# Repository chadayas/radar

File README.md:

# In Progress
repo will stay little messy till hardware design is finished.

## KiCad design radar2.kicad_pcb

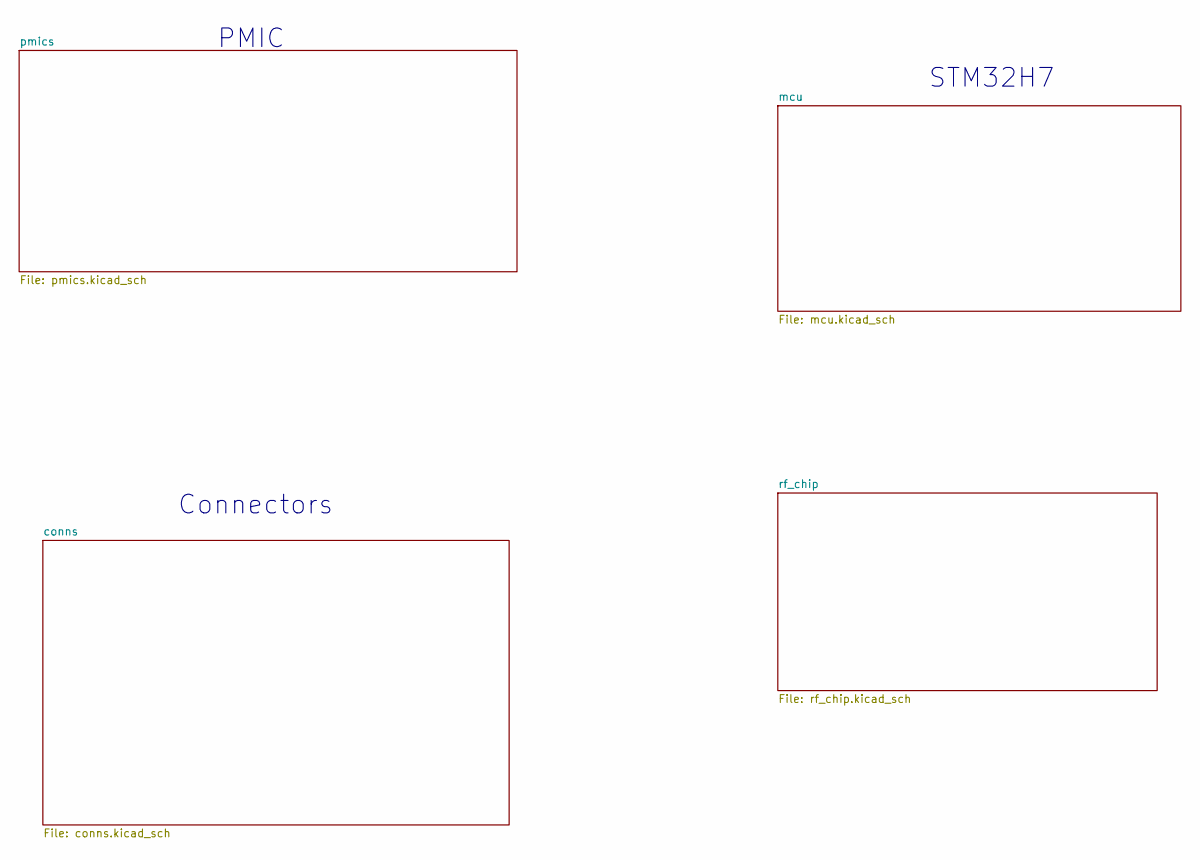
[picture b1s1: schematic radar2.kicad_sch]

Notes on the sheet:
PMIC
Connectors
STM32H7

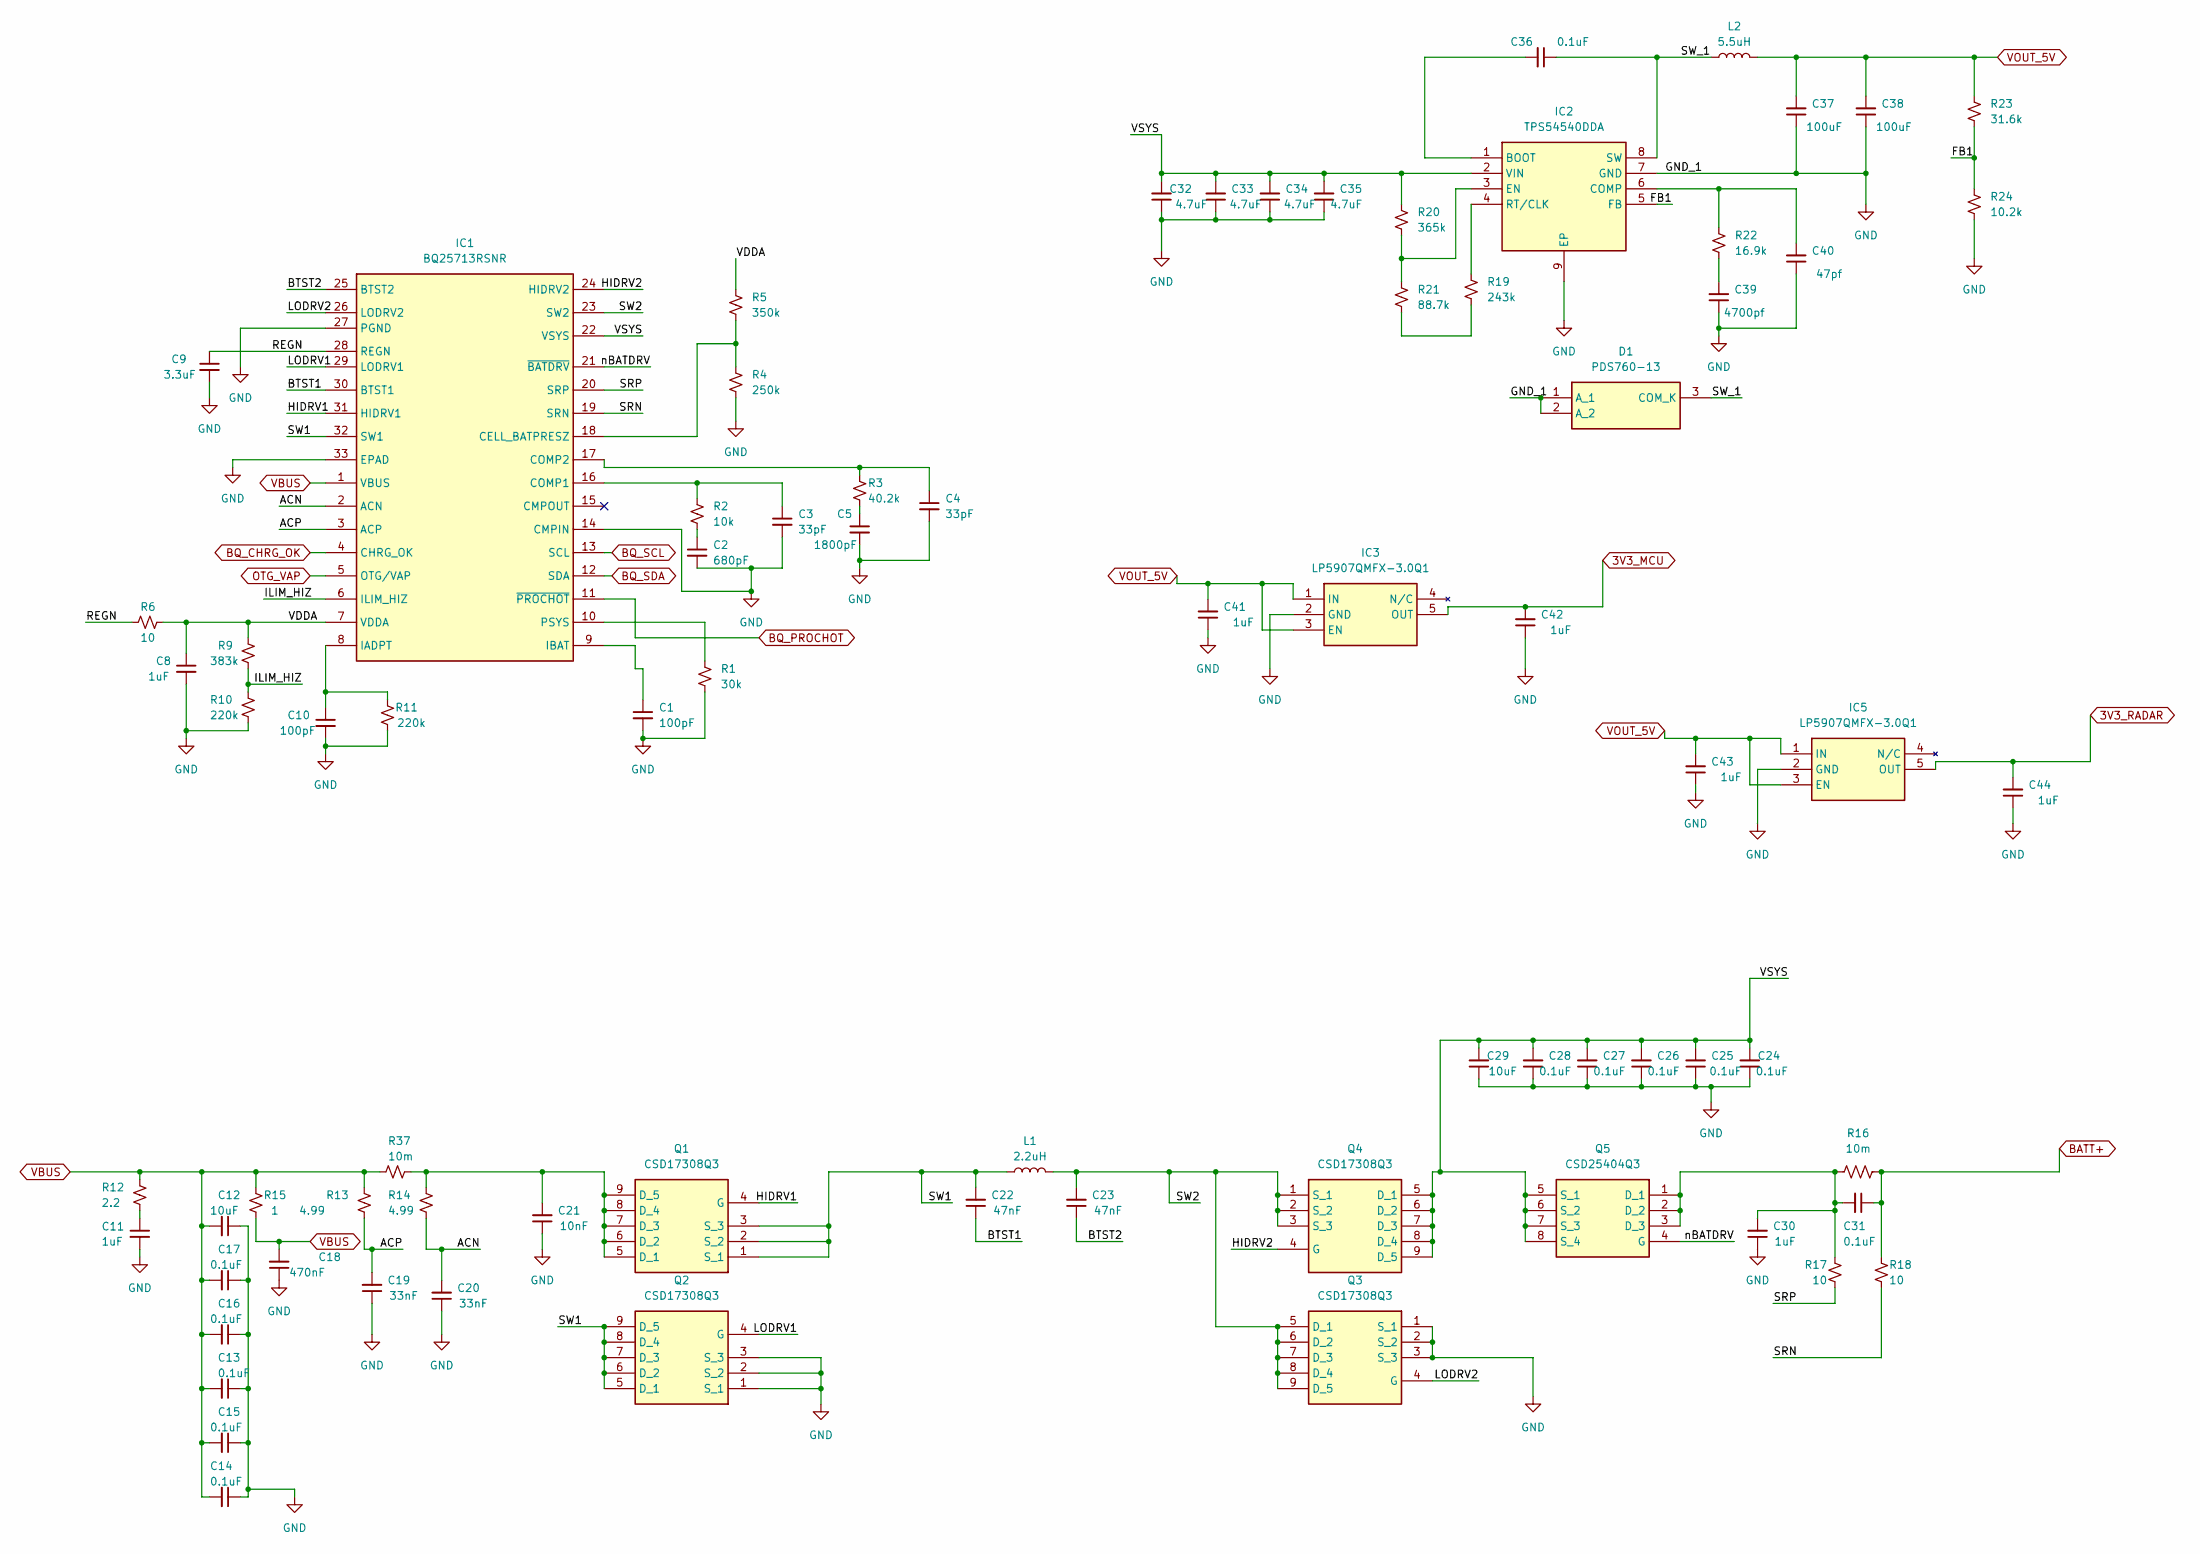
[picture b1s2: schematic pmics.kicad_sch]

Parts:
C1, C10: 100pF; C_0402_1005Metric
C2: 680pF; C_0402_1005Metric
C3, C4: 33pF; C_0402_1005Metric
C5: 1800pF; C_0402_1005Metric
C8, C30: 1uF; C_0402_1005Metric
C9: 3.3uF; C_0402_1005Metric
C11, C41, C42, C43, C44: 1uF; C_0603_1608Metric
C12: 10uF; C_0402_1005Metric
C13, C14, C15, C16, C17, C24, C25, C26, C27, C28, C31: 0.1uF; C_0402_1005Metric
C18: 470nF; C_0402_1005Metric
C19, C20: 33nF; C_0603_1608Metric
C21: 10nF; C_0603_1608Metric
C22, C23: 47nF; C_0402_1005Metric
C29: 10uF; C_0603_1608Metric
C32, C33, C34, C35: 4.7uF; C_0603_1608Metric
C36: 0.1uF; C_0603_1608Metric
C37, C38: 100uF; C_0603_1608Metric
C39: 4700pf; C_0603_1608Metric
C40: 47pf; C_0603_1608Metric
D1: PDS760-13; POWERDI5; Mouser Part Number 621-PDS760-F
IC1: BQ25713RSNR; QFN40P400X400X80-33N-D; Mouser Part Number 595-BQ25713RSNR
IC2: TPS54540DDA; SOIC127P600X170-9N; Mouser Part Number 595-TPS54540DDA
IC3, IC5: LP5907QMFX-3.0Q1; SOT95P280X145-5N; Mouser Part Number 595-LP5907QMFX-3.0Q1
L1: 2.2uH; INDPM9785X300N
L2: 5.5uH; L_0603_1608Metric
Q1, Q2, Q3, Q4: CSD17308Q3; Mouser Part Number 595-CSD17308Q3
Q5: CSD25404Q3; DQG_VSON-CLIP; Mouser Part Number 595-CSD25404Q3
R1: 30k; R_0402_1005Metric
R2: 10k; R_0402_1005Metric
R3: 40.2k; R_0402_1005Metric
R4: 250k; R_0402_1005Metric
R5: 350k; R_0402_1005Metric
R6, R17, R18: 10; R_0402_1005Metric
R9: 383k; R_0402_1005Metric
R10, R11: 220k; R_0402_1005Metric
R12: 2.2; R_0603_1608Metric
R13, R14: 4.99; R_0603_1608Metric
R15: 1; R_0603_1608Metric
R16: 10m; R_0402_1005Metric
R19: 243k; R_0603_1608Metric
R20: 365k; R_0603_1608Metric
R21: 88.7k; R_0603_1608Metric
R22: 16.9k; R_0603_1608Metric
R23: 31.6k; R_0603_1608Metric
R24: 10.2k; R_0603_1608Metric
R37: 10m; R_0603_1608Metric

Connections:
3V3_MCU: C42.2, IC3.5 (OUT); also elsewhere on the board
/pmics/ACN: C20.2, IC1.2 (ACN), R14.1
/pmics/ACP: C19.2, IC1.3 (ACP), R13.1
/pmics/BTST1: C22.1, IC1.30 (BTST1)
/pmics/BTST2: C23.1, IC1.25 (BTST2)
/pmics/FB1: IC2.5 (FB), R23.2, R24.1
/pmics/HIDRV1: IC1.31 (HIDRV1), Q1.4 (G)
/pmics/HIDRV2: IC1.24 (HIDRV2), Q4.4 (G)
/pmics/ILIM_HIZ: IC1.6 (ILIM_HIZ), R9.2, R10.2
/pmics/LODRV1: IC1.29 (LODRV1), Q2.4 (G)
/pmics/LODRV2: IC1.26 (LODRV2), Q3.4 (G)
/pmics/REGN: C9.1, IC1.28 (REGN), R6.2
/pmics/SRN: IC1.19 (SRN), R18.2
/pmics/SRP: IC1.20 (SRP), R17.1
/pmics/SW1: C22.2, IC1.32 (SW1), L1.1, Q1.1 (S_1), Q1.2 (S_2), Q1.3 (S_3), Q2.5 (D_1), Q2.6 (D_2), Q2.7 (D_3), Q2.8 (D_4), Q2.9 (D_5)
/pmics/SW2: C23.2, IC1.23 (SW2), L1.2, Q3.5 (D_1), Q3.6 (D_2), Q3.7 (D_3), Q3.8 (D_4), Q3.9 (D_5), Q4.1 (S_1), Q4.2 (S_2), Q4.3 (S_3)
/pmics/SW_1: C36.1, D1.3 (COM_K), IC2.8 (SW), L2.1
/pmics/VDDA: C8.1, IC1.7 (VDDA), R5.2, R6.1, R9.1
/pmics/VSYS: C24.2, C25.2, C26.2, C27.2, C28.2, C29.2, C32.2, C33.2, C34.2, C35.2, IC1.22 (VSYS), IC2.2 (VIN), Q4.5 (D_1), Q4.6 (D_2), Q4.7 (D_3), Q4.8 (D_4), Q4.9 (D_5), Q5.5 (S_1), Q5.6 (S_2), Q5.7 (S_3), Q5.8 (S_4), Q5.9, R20.1
/pmics/nBATDRV: IC1.21 (~BATDRV), Q5.4 (G)
BATT+: C31.1, R16.2, R18.1; also elsewhere on the board
BQ_CHRG_OK: IC1.4 (CHRG_OK); also elsewhere on the board
BQ_PROCHOT: IC1.11 (~PROCHOT); also elsewhere on the board
BQ_SCL: IC1.13 (SCL); also elsewhere on the board
BQ_SDA: IC1.12 (SDA); also elsewhere on the board
unnamed: C2.1, R2.2
unnamed: C5.1, R3.1
unnamed: C11.1, R12.1
unnamed: C39.2, R22.2
unnamed: IC1.18 (CELL_BATPRESZ), R4.2, R5.1
unnamed: C3.1, IC1.16 (COMP1), R2.1
unnamed: C4.1, IC1.17 (COMP2), R3.2
unnamed: C10.1, IC1.8 (IADPT), R11.1
unnamed: C1.1, IC1.9 (IBAT)
unnamed: IC1.10 (PSYS), R1.1
unnamed: C36.2, IC2.1 (BOOT)
unnamed: C40.2, IC2.6 (COMP), R22.1
unnamed: IC2.3 (EN), R20.2, R21.1
unnamed: IC2.4 (RT/CLK), R19.1
unnamed: C21.2, Q1.5 (D_1), Q1.6 (D_2), Q1.7 (D_3), Q1.8 (D_4), Q1.9 (D_5), R14.2, R37.2
unnamed: C30.2, C31.2, Q5.1 (D_1), Q5.2 (D_2), Q5.3 (D_3), R16.1, R17.2
unnamed: R19.2, R21.2
OTG_VAP: IC1.5 (OTG/VAP)
VBUS: C12.2, C13.2, C14.2, C15.2, C16.2, C17.2, C18.2, IC1.1 (VBUS), R12.2, R13.2, R15.1, R15.2, R37.1; also elsewhere on the board
VOUT_5V: C37.2, C38.2, C41.2, C43.2, IC3.1 (IN), IC3.3 (EN), IC5.1 (IN), IC5.3 (EN), L2.2, R23.1; also elsewhere on the board

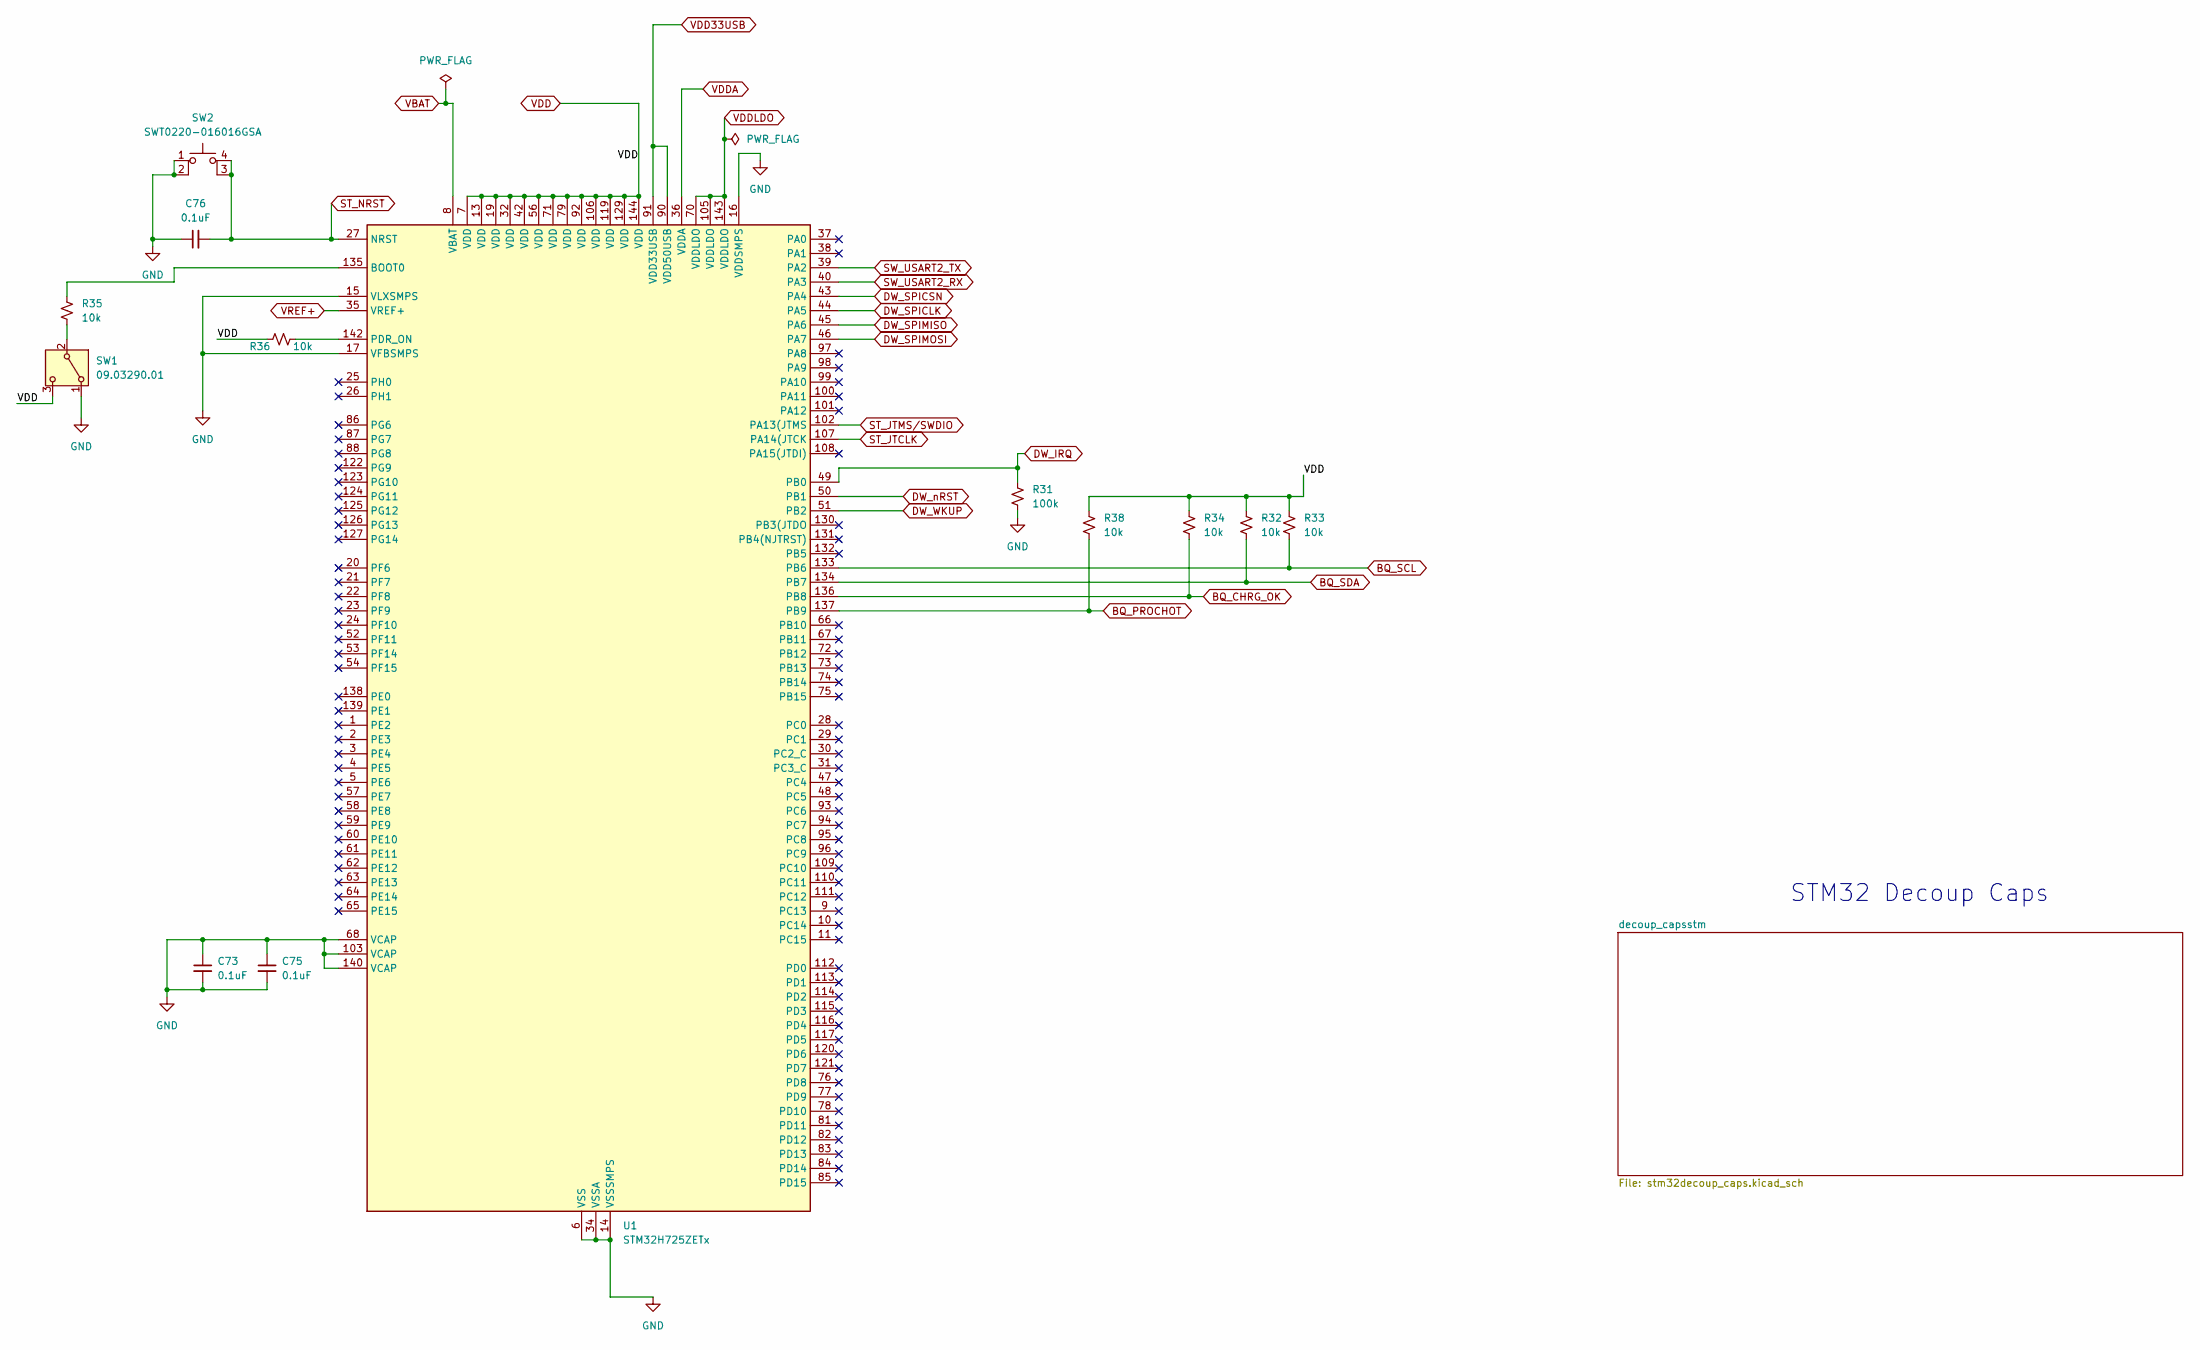
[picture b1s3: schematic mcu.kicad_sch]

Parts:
C73, C75, C76: 0.1uF; C_0603_1608Metric
R31: 100k; R_0603_1608Metric
R32, R33, R34, R35, R36, R38: 10k; R_0603_1608Metric
SW1: 09.03290.01; 090329001
SW2: SWT0220-016016GSA; GSB
U1: STM32H725ZETx; LQFP-144_20x20mm_P0.5mm

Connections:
3V3_MCU: R32.1, R33.2, R34.1, R36.2, R38.1, SW1.3 (C), U1.7 (VDD), U1.13 (VDD), U1.19 (VDD), U1.32 (VDD), U1.35 (VREF+), U1.36 (VDDA), U1.42 (VDD), U1.56 (VDD), U1.71 (VDD), U1.79 (VDD), U1.90 (VDD50USB), U1.91 (VDD33USB), U1.92 (VDD), U1.106 (VDD), U1.119 (VDD), U1.129 (VDD), U1.144 (VDD); also elsewhere on the board
BQ_CHRG_OK: R34.2, U1.136 (PB8); also elsewhere on the board
BQ_PROCHOT: R38.2, U1.137 (PB9); also elsewhere on the board
BQ_SCL: R33.1, U1.133 (PB6); also elsewhere on the board
BQ_SDA: R32.2, U1.134 (PB7); also elsewhere on the board
DW_IRQ: R31.1, U1.49 (PB0); also elsewhere on the board
DW_SPICLK: U1.44 (PA5); also elsewhere on the board
DW_SPICSN: U1.43 (PA4); also elsewhere on the board
DW_SPIMISO: U1.45 (PA6); also elsewhere on the board
DW_SPIMOSI: U1.46 (PA7); also elsewhere on the board
DW_WKUP: U1.51 (PB2); also elsewhere on the board
DW_nRST: U1.50 (PB1); also elsewhere on the board
unnamed: R35.2, SW1.2 (B)
unnamed: R35.1, U1.135 (BOOT0)
unnamed: R36.1, U1.142 (PDR_ON)
ST_JTCLK: U1.107 (PA14(JTCK); also elsewhere on the board
ST_JTMS/SWDIO: U1.102 (PA13(JTMS); also elsewhere on the board
ST_NRST: C76.2, SW2.3 (K), SW2.4 (A), U1.27 (NRST); also elsewhere on the board
SW_USART2_RX: U1.40 (PA3); also elsewhere on the board
SW_USART2_TX: U1.39 (PA2); also elsewhere on the board
VBAT: U1.8 (VBAT); also elsewhere on the board
VDDLDO: U1.70 (VDDLDO), U1.105 (VDDLDO), U1.143 (VDDLDO); also elsewhere on the board

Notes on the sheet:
STM32 Decoup Caps

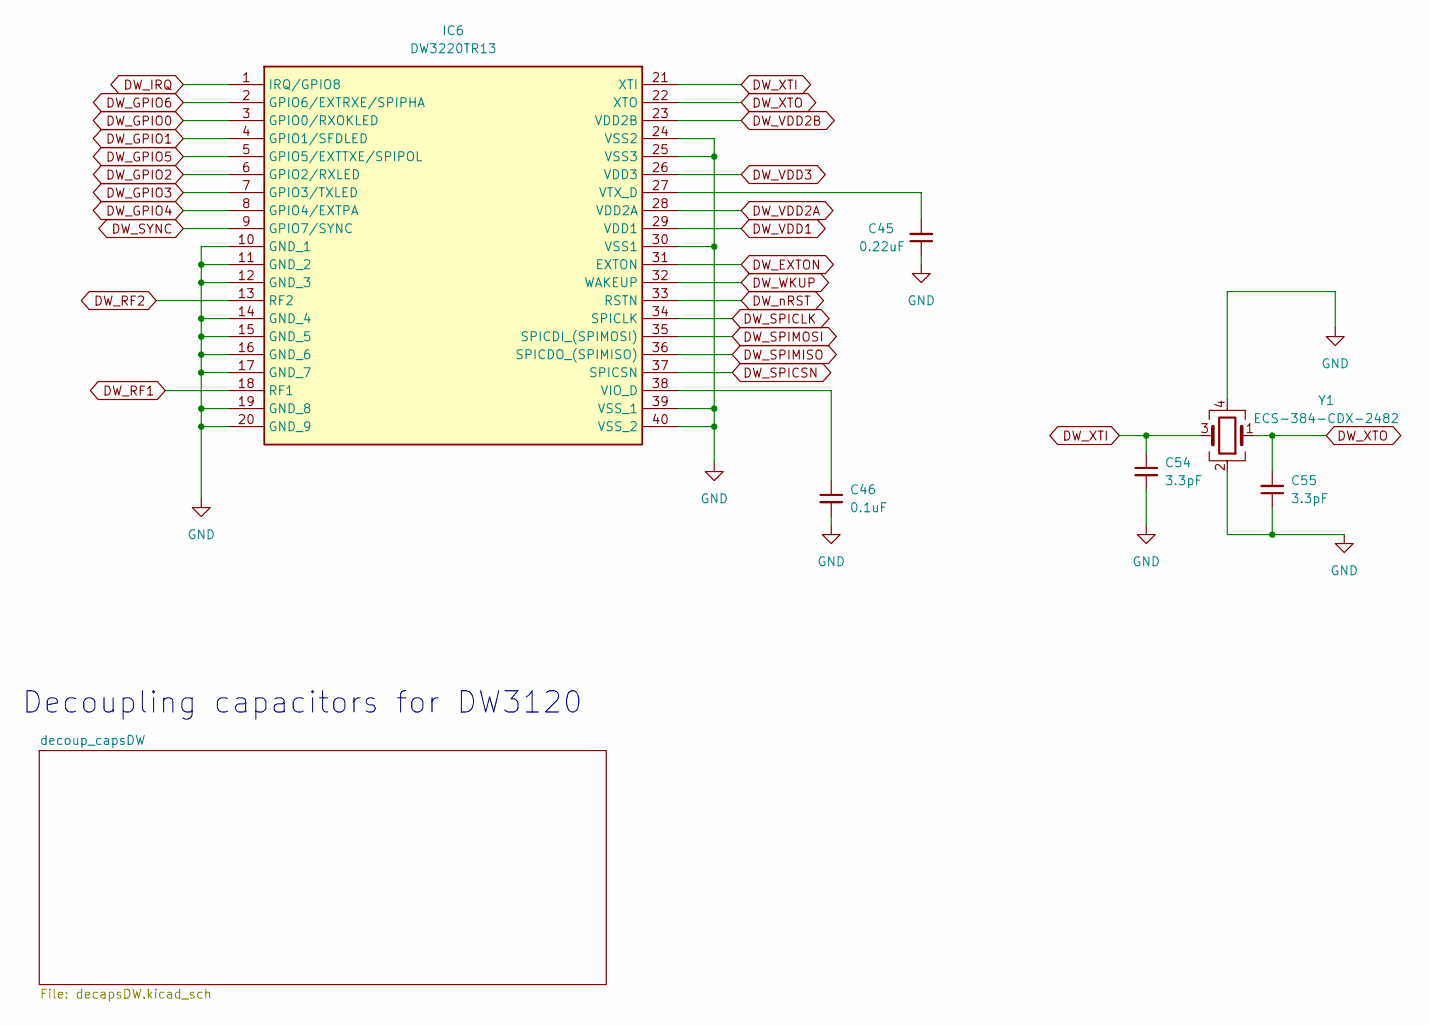
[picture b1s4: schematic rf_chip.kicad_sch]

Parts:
C45: 0.22uF; C_0402_1005Metric
C46: 0.1uF; C_0402_1005Metric
C54, C55: 3.3pF; C_0402_1005Metric
IC6: DW3220TR13; DW3220TR13-1; Mouser Part Number 772-DW3220TR13
Y1: ECS-384-CDX-2482; Crystal_SMD_2016-4Pin_2.0x1.6mm

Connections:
DW_EXTON: IC6.31 (EXTON)
DW_GPIO0: IC6.3 (GPIO0/RXOKLED)
DW_GPIO1: IC6.4 (GPIO1/SFDLED)
DW_GPIO2: IC6.6 (GPIO2/RXLED)
DW_GPIO3: IC6.7 (GPIO3/TXLED)
DW_GPIO4: IC6.8 (GPIO4/EXTPA)
DW_GPIO5: IC6.5 (GPIO5/EXTTXE/SPIPOL)
DW_GPIO6: IC6.2 (GPIO6/EXTRXE/SPIPHA)
DW_IRQ: IC6.1 (IRQ/GPIO8); also elsewhere on the board
DW_RF1: IC6.18 (RF1); also elsewhere on the board
DW_RF2: IC6.13 (RF2); also elsewhere on the board
DW_SPICLK: IC6.34 (SPICLK); also elsewhere on the board
DW_SPICSN: IC6.37 (SPICSN); also elsewhere on the board
DW_SPIMISO: IC6.36 (SPICDO_(SPIMISO)); also elsewhere on the board
DW_SPIMOSI: IC6.35 (SPICDI_(SPIMOSI)); also elsewhere on the board
DW_SYNC: IC6.9 (GPIO7/SYNC)
DW_WKUP: IC6.32 (WAKEUP); also elsewhere on the board
DW_XTI: C54.1, IC6.21 (XTI), Y1.3
DW_XTO: C55.2, IC6.22 (XTO), Y1.1
DW_nRST: IC6.33 (RSTN); also elsewhere on the board
unnamed: C46.1, IC6.38 (VIO_D)
unnamed: C45.2, IC6.27 (VTX_D)

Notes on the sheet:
Decoupling capacitors for DW3120

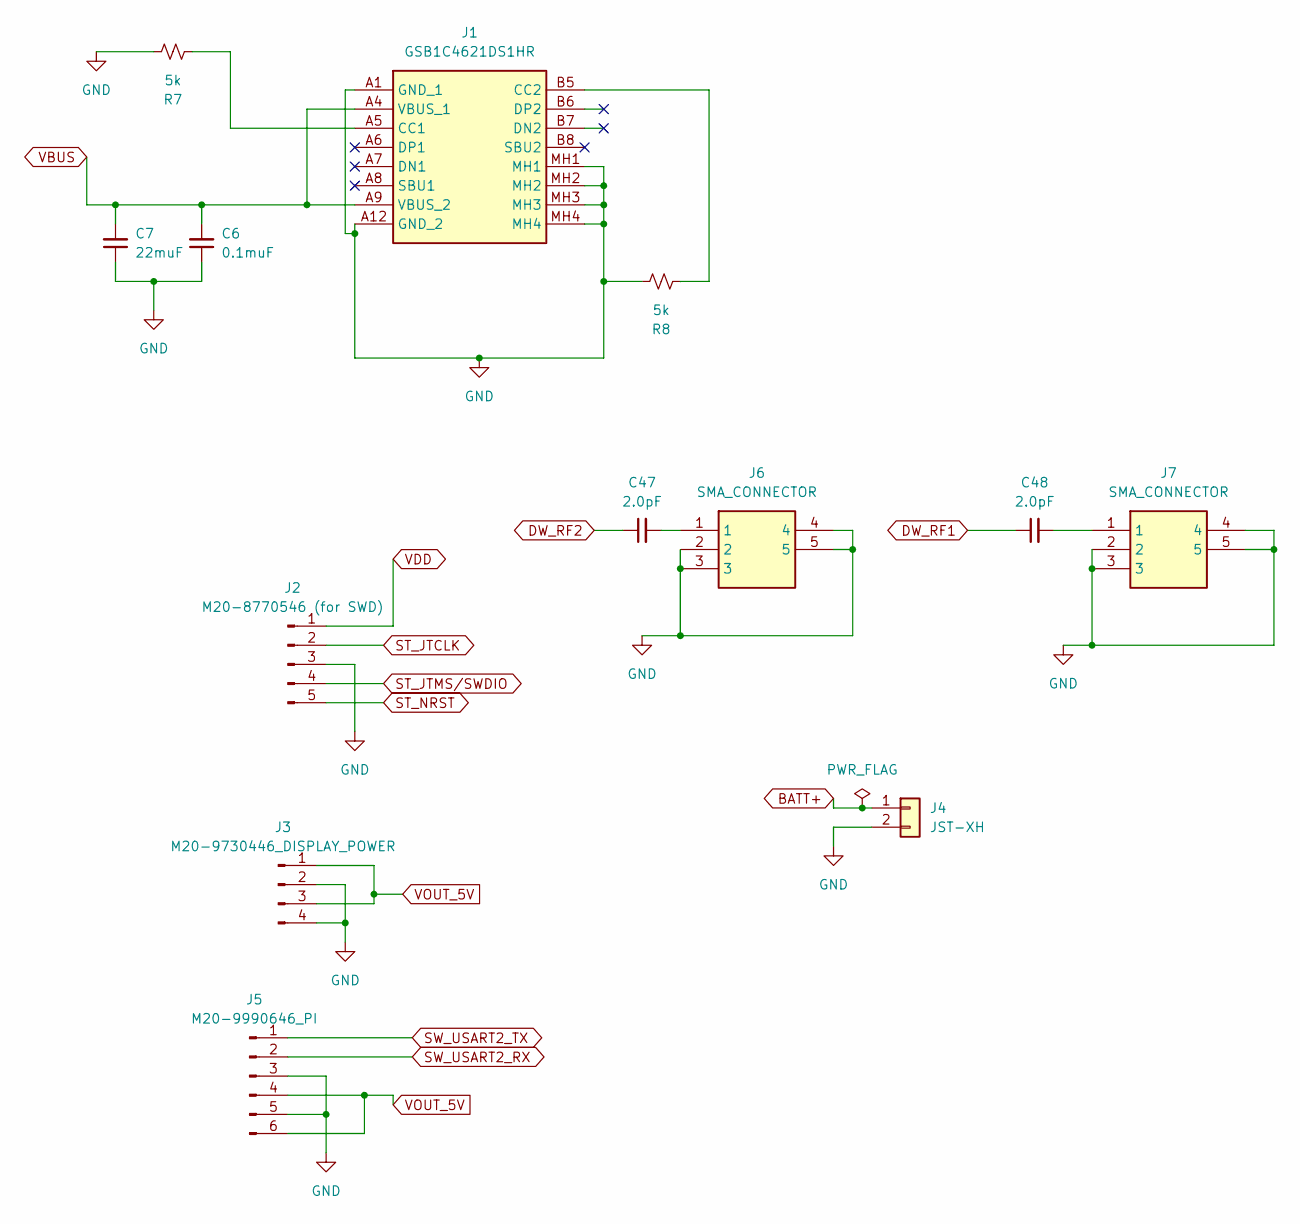
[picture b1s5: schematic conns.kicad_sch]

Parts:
C6: 0.1muF; C_0603_1608Metric
C7: 22muF; C_0603_1608Metric
C47, C48: 2.0pF; C_0402_1005Metric
J1: GSB1C4621DS1HR; GSB; Manufacturer_Part_Number GSB1C4621DS1HR
J2: M20-8770546 (for SWD); PinHeader_1x05_P2.54mm_Vertical
J3: M20-9730446_DISPLAY_POWER; PinHeader_1x04_P2.54mm_Vertical
J4: JST-XH; JST_XH_B2B-XH-AM_1x02_P2.50mm_Vertical
J5: M20-9990646_PI; PinHeader_1x06_P2.54mm_Vertical
J6, J7: SMA_CONNECTOR; SMACONNECTOR; Mouser Part Number 471-SMACONNECTOR
R7, R8: 5k; R_0603_1608Metric

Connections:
3V3_MCU: J2.1; also elsewhere on the board
BATT+: J4.1; also elsewhere on the board
DW_RF1: C48.1; also elsewhere on the board
DW_RF2: C47.1; also elsewhere on the board
unnamed: C47.2, J6.1
unnamed: C48.2, J7.1
unnamed: J1.A5 (CC1), R7.1
unnamed: J1.B5 (CC2), R8.1
ST_JTCLK: J2.2; also elsewhere on the board
ST_JTMS/SWDIO: J2.4; also elsewhere on the board
ST_NRST: J2.5; also elsewhere on the board
SW_USART2_RX: J5.2; also elsewhere on the board
SW_USART2_TX: J5.1; also elsewhere on the board
VBUS: C6.2, C7.2, J1.A4 (VBUS_1), J1.A9 (VBUS_2); also elsewhere on the board
VOUT_5V: J3.1, J3.3, J5.4, J5.6; also elsewhere on the board

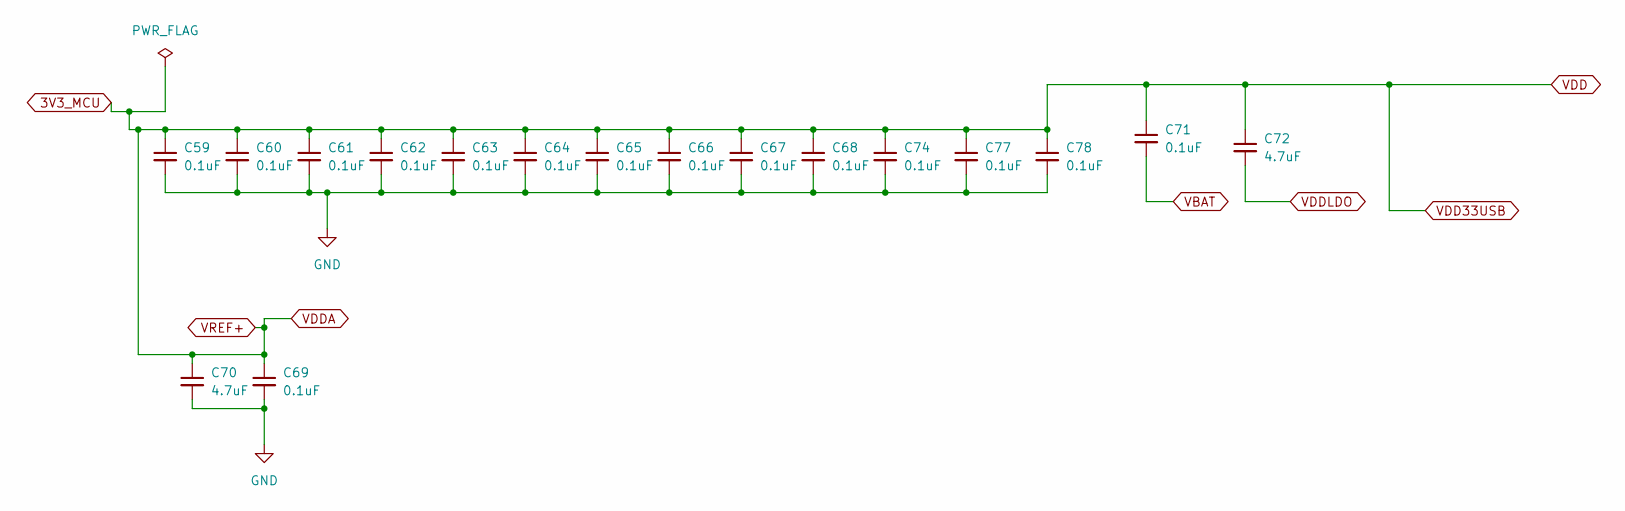
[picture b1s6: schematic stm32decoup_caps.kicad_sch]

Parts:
C59, C60, C61, C62, C63, C64, C65, C66, C67, C68, C69, C71, C74, C77, C78: 0.1uF; C_0402_1005Metric
C70, C72: 4.7uF; C_0402_1005Metric

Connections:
3V3_MCU: C59.1, C60.1, C61.1, C62.1, C63.1, C64.1, C65.1, C66.1, C67.1, C68.1, C69.1, C70.1, C71.1, C72.1, C74.1, C77.1, C78.1; also elsewhere on the board
VBAT: C71.2; also elsewhere on the board
VDDLDO: C72.2; also elsewhere on the board

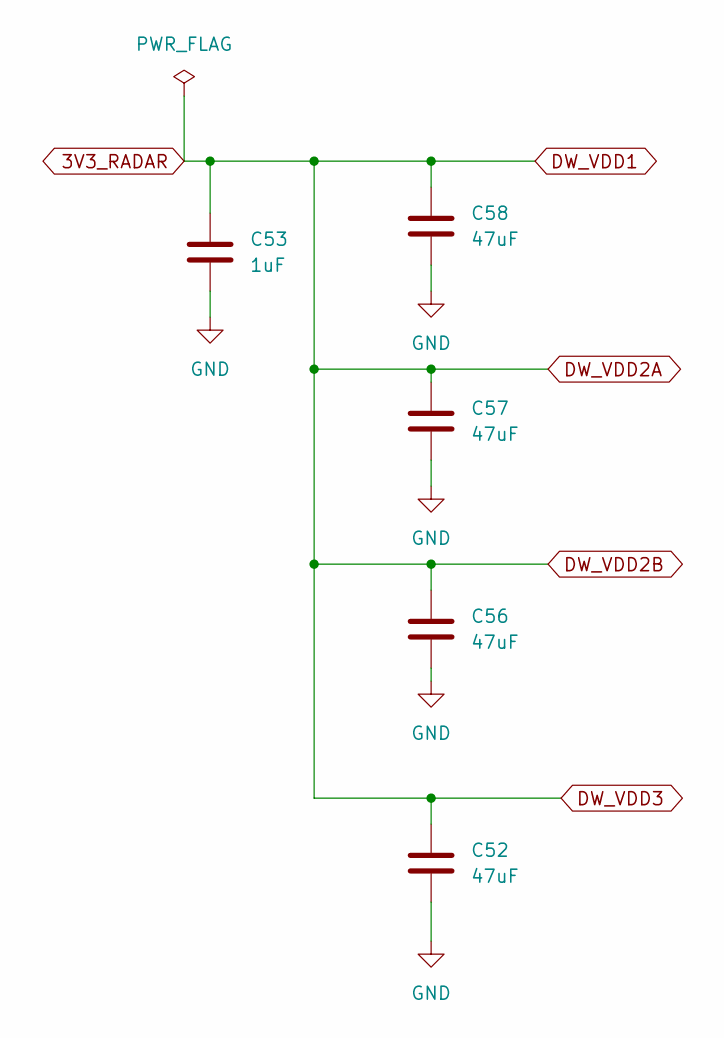
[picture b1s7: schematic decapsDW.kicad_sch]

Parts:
C52, C56, C57, C58: 47uF; C_0603_1608Metric
C53: 1uF; C_0603_1608Metric

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
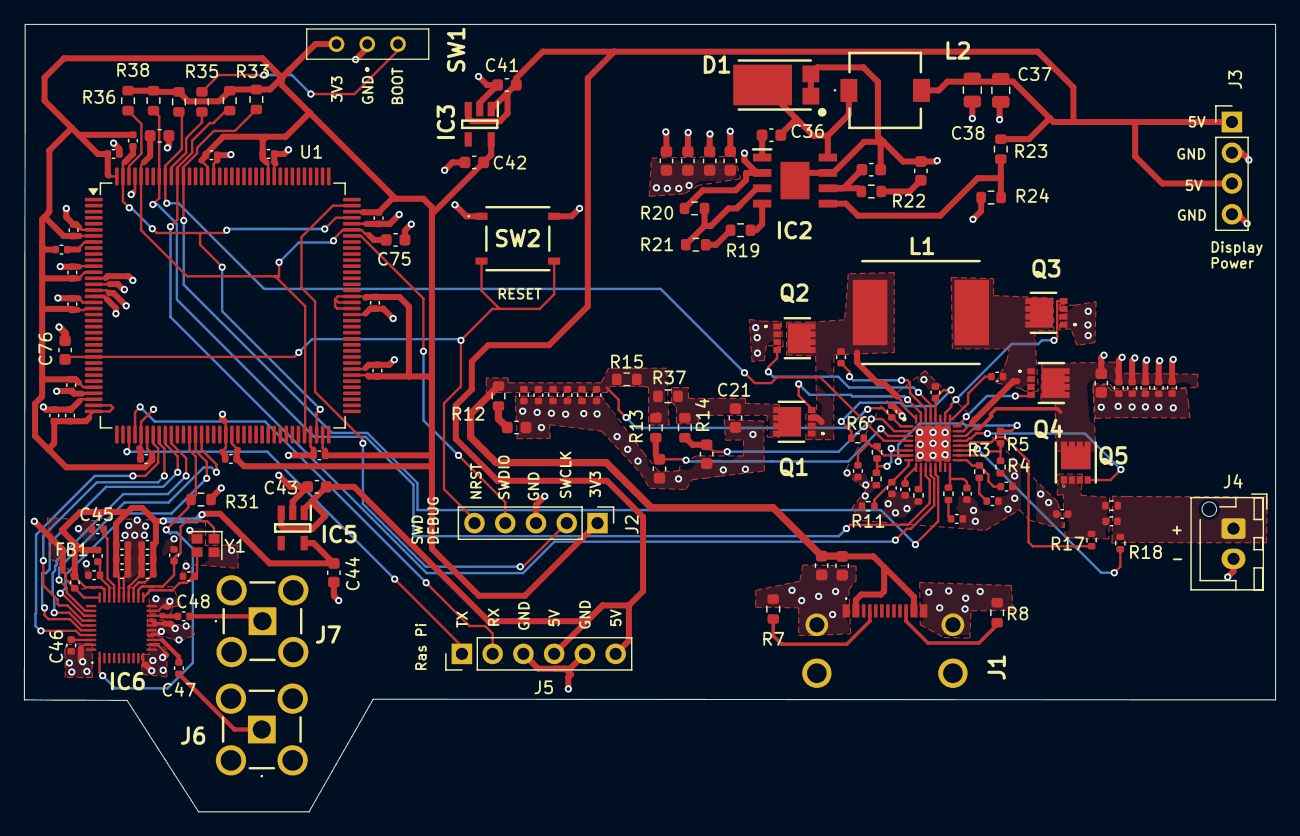
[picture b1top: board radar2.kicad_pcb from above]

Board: 4 copper layers, 103.4 x 65.0 mm, 135 parts (0 on the bottom side), 75 nets.

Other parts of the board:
C49: 0.1uF; C_0402_1005Metric
C50: 4.7nF; C_0402_1005Metric
C51: 10uF; C_0402_1005Metric
FB1: 33; C_0402_1005Metric

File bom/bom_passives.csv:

Value,Package,Qty,Designators,Mfr,Mfr Part Number,Dielectric,Rating,Tol,Notes
0.1uF,C_0402,30,"C13,C14,C15,C16,C17,C24,C25,C26,C27,C28,C31,C46,C49,C52,C58,C59,C60,C61,C62,C63,C64,C65,C66,C67,C68,C69,C71,C74,C77,C78",Samsung,CL05B104KO5NNNC,X7R,16V,10%,
0.1uF,C_0603,5,"C6,C36,C73,C75,C76",Samsung,CL10B104KO8NNNC,X7R,16V,10%,
1uF,C_0603,5,"C11,C41,C42,C43,C44",Samsung,CL10B105KO8NNNC,X7R,16V,10%,
4.7uF,C_0603,4,"C32,C33,C34,C35",Samsung,CL10A475KO8NNNC,X5R,16V,10%,
10uF,C_0402,3,"C12,C51,C57",Samsung,CL05A106KQ5NNNC,X5R,6.3V,,verify stock; heavy DC-bias at 3V3 - 0603 recommended
4.7nF,C_0402,3,"C50,C53,C56",Samsung,CL05B472KO5NNNC,X7R,16V,10%,
100pF,C_0402,2,"C1,C10",Samsung,CL05C101JB5NNNC,C0G,50V,5%,
100uF,C_0603,2,"C37,C38",Samsung,,X5R,16V,10%,"100uF NOT available in 0603 -> move to 0805/1206 or split, then pick MPN"
1uF,C_0402,2,"C8,C30",Samsung,CL05B105KO5NNNC,X7R,16V,10%,
2.0pF,C_0402,2,"C47,C48",Samsung,CL05C2R0CB5NNNC,C0G,50V,±0.25pF,RF path
3.3pF,C_0402,2,"C54,C55",Samsung,CL05C3R3CB5NNNC,C0G,50V,±0.25pF,xtal load cap (tight tol)
33nF,C_0603,2,"C19,C20",Samsung,CL10B333KO8NNNC,X7R,16V,10%,
33pF,C_0402,2,"C3,C4",Samsung,CL05C330JB5NNNC,C0G,50V,5%,
4.7uF,C_0402,2,"C70,C72",Samsung,CL05A475KO5NNNC,X5R,16V,10%,
47nF,C_0402,2,"C22,C23",Samsung,CL05B473KO5NNNC,X7R,16V,10%,
0.22uF,C_0402,1,C45,Samsung,CL05B224KO5NNNC,X7R,16V,10%,
10nF,C_0603,1,C21,Samsung,CL10B103KO8NNNC,X7R,16V,10%,
10uF,C_0603,1,C29,Samsung,CL10A106KO8NQNC,X5R,16V,,"verified Mouser; if rail<=5V, CL10A106KP8NNNC (10V, LCSC C19702) is cheaper"
1800pF,C_0402,1,C5,Samsung,CL05B182KO5NNNC,X7R,16V,10%,
22uF,C_0603,1,C7,Samsung,CL10A226KP8NNNC,X5R,10V,,verify suffix (NNNC/NQNC); 0805 safer for VBUS margin
3.3uF,C_0402,1,C9,Samsung,CL05A335KO5NNNC,X5R,16V,10%,
4700pf,C_0603,1,C39,Samsung,CL10B472KO8NNNC,X7R,16V,10%,
470nF,C_0402,1,C18,Samsung,CL05B474KO5NNNC,X7R,16V,10%,
47pf,C_0603,1,C40,Samsung,CL10C470JB8NNNC,C0G,50V,5%,
680pF,C_0402,1,C2,Samsung,CL05B681KO5NNNC,X7R,16V,10%,
10k,R_0603,6,"R32,R33,R34,R35,R36,R38",Yageo,RC0603FR-0710KL,,1/10W,1%,
10,R_0402,3,"R6,R17,R18",Yageo,RC0402FR-0710RL,,1/16W,1%,
220k,R_0402,2,"R10,R11",Yageo,RC0402FR-07220KL,,1/16W,1%,verify 1% stock (E24 value)
4.99,R_0603,2,"R13,R14",Yageo,RC0603FR-074R99L,,1/10W,1%,
5k,R_0603,2,"R7,R8",Yageo,RC0603FR-074K99L,,1/10W,1%,5k not E96 -> sub 4.99k
1,R_0603,1,R15,Yageo,RC0603FR-071RL,,1/10W,1%,
10.2k,R_0603,1,R24,Yageo,RC0603FR-0710K2L,,1/10W,1%,
100k,R_0603,1,R31,Yageo,RC0603FR-07100KL,,1/10W,1%,
10k,R_0402,1,R2,Yageo,RC0402FR-0710KL,,1/16W,1%,
10m,R_0402,1,R16,,,—,1%,—,"10mOhm SENSE: pick by power vs peak I (e.g. Bourns CR/Panasonic ERJ, ≥adequate W)"
10m,R_0603,1,R37,,,—,1%,—,"10mOhm SENSE: pick by power vs peak I (e.g. Bourns CR/Panasonic ERJ, ≥adequate W)"
16.9k,R_0603,1,R22,Yageo,RC0603FR-0716K9L,,1/10W,1%,
2.2,R_0603,1,R12,Yageo,RC0603FR-072R2L,,1/10W,1%,
243k,R_0603,1,R19,Yageo,RC0603FR-07243KL,,1/10W,1%,
250k,R_0402,1,R4,Yageo,RC0402FR-07249KL,,1/16W,1%,250k not E96 -> sub 249k
30k,R_0402,1,R1,Yageo,RC0402FR-0730KL,,1/16W,1%,verify 1% stock (E24 value)
31.6k,R_0603,1,R23,Yageo,RC0603FR-0731K6L,,1/10W,1%,
350k,R_0402,1,R5,Yageo,RC0402FR-07348KL,,1/16W,1%,350k not E96 -> sub 348k
365k,R_0603,1,R20,Yageo,RC0603FR-07365KL,,1/10W,1%,
383k,R_0402,1,R9,Yageo,RC0402FR-07383KL,,1/16W,1%,
40.2k,R_0402,1,R3,Yageo,RC0402FR-0740K2L,,1/16W,1%,
88.7k,R_0603,1,R21,Yageo,RC0603FR-0788K7L,,1/10W,1%,
2.2uH,INDPM9785X300N,1,L1,,,,,,select by Isat/Irms>=peak coil current
5.5uH,L_0603,1,L2,,,,,,select by Isat/Irms>=peak coil current
33,C_0402,1,FB1,,,,,,ferrite 33ohm@100MHz + rated current

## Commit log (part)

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2026-05-26 inital commit
2026-05-28 expanding size of schematic
2026-05-31 finished power sheet
2026-06-02 adding another sheet, stm32h7 core
2026-06-02 ignore
2026-06-12 rm stm32h7 going with awr1843 for our needs
2026-06-14 finished tps symbol
2026-06-14 edits on TPS, one component was not in stock had to find something similar
2026-06-14 renaming LMS
2026-06-15 starting on LP877 buck converter
2026-06-16 rm the custom made symbols as TI has them already made with the footprints, goofy mistake
2026-06-16 adding in the new symbol dirs
2026-06-19 using ultra lib symbols instead of custom and adding to sym table
2026-06-19 working on power again with new compoenets
2026-06-20 finished buck converter, new sheet for ldo and step down
2026-06-20 adding our charge controller and usbc connector
2026-06-20 finished BQ charge controller
2026-06-21 finishing power sschematics
2026-06-21 squasing ERC errors
2026-06-22 squased errors going over supply desgin
2026-06-22 enabling OTG pin and PMID for 5v output
2026-06-24 some fixes
2026-06-26 editing reset_n pin on LMS3635
2026-06-26 making unit design for AWR1843, starting with GND, voltage, I2C and GPIO
2026-06-28 working on connectors
2026-06-28 finishing connectors
2026-06-29 grabbing flash footprint and symbol
2026-06-29 finishing flash schematic
2026-06-30 decoup and lc schematics
